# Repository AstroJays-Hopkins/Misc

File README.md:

# Misc

Small collection of utilities that don't have official repositories in the
Hopkins Rocketry Github org yet. These are experimental and may set your house on
fire, kill your pets, or do other horrible things. Consider yourself warned.

## DartPlot

(Avionics)

Visualize the runtime sensor logs (in our csv format).

## Schematics

(Avionics)

Temporary schematics until better quality ones can be drawn. Move these out as
they mature.

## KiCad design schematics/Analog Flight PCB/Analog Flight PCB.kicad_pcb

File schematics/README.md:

# Schematics

Temporary avionics schematics that haven't been reviewed yet, but need to be
saved for documentation purposes.

## Listing

- Ignition-System - Provisional ignition control box ("football") schematics.
  Inaccurate due to missing wires in football and broken conenctions.
- Prop-Avionics - Schematics for the propulsion avionics system and DAQ plane
- SolenoidRelay1 - Schematic for the solenoid control relay for connection to
  the raspberry pi.
- Transole - Prototype transistor based solenoid switching using GPIO level
  outputs and a heckin' large transistor (n-channel MOSFET). This is a *untested
  prototype* and should not be used in production until more research has been
  completed. Credit Sasha and Lin for research and design

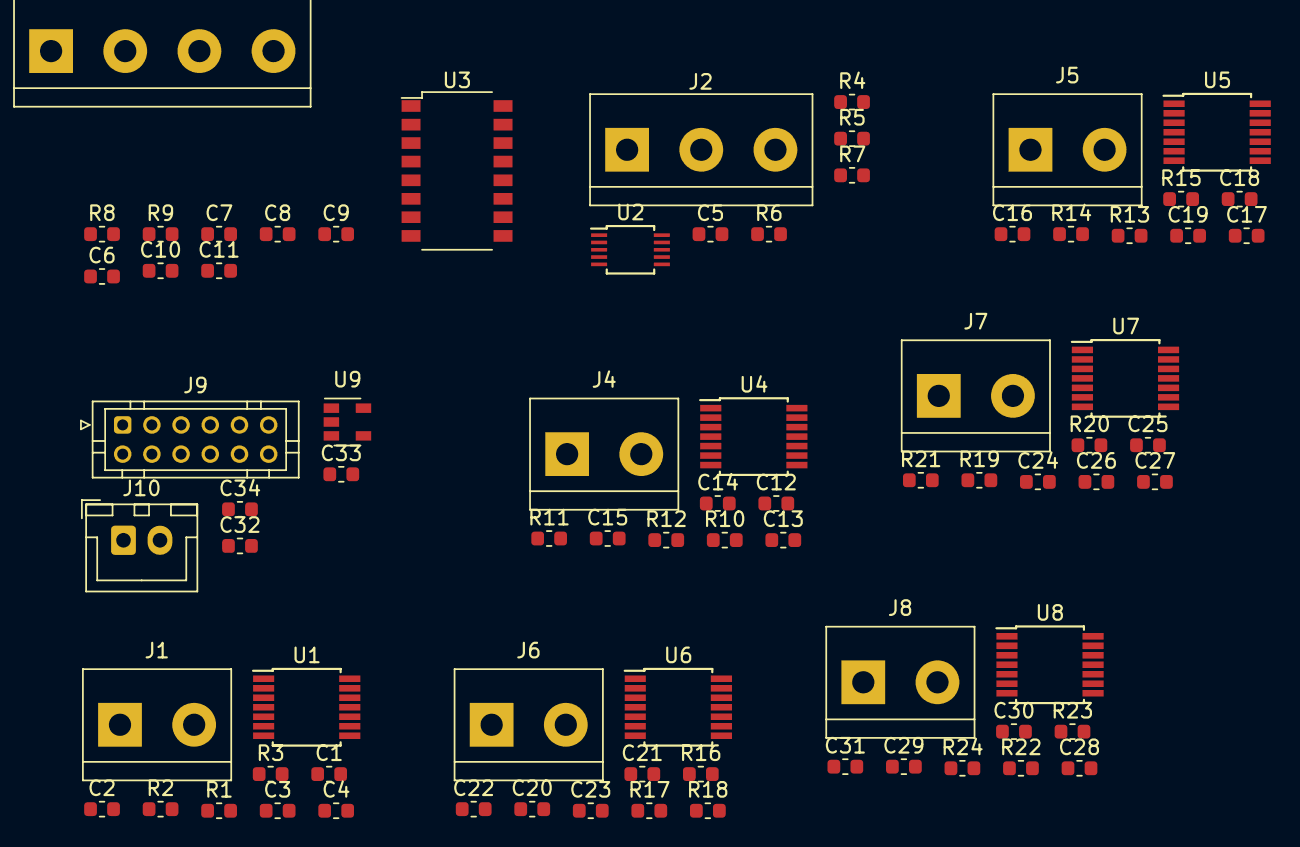
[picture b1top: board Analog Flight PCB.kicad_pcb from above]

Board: 2 copper layers, 77 parts (0 on the bottom side), 58 nets, no tracks yet.

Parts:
C1, C3, C12, C14, C16, C18, C20, C22, C24, C26, C28, C30, C34: 0.01u; C_0603_1608Metric
C2, C4, C6, C7, C10, C13, C15, C17, C19, C21, C23, C25, C27, C29, C31: 0.1u; C_0603_1608Metric
C5, C9, C11: 1u; C_0603_1608Metric
C8: 680p; C_0603_1608Metric
C32, C33: 2.2u; C_0603_1608Metric
J1, J4, J5, J6, J7, J8: Screw_Terminal_01x02; TerminalBlock_bornier-2_P5.08mm
J2: Screw_Terminal_01x03; TerminalBlock_bornier-3_P5.08mm
J3: Screw_Terminal_01x04; TerminalBlock_bornier-4_P5.08mm
J9: Conn_02x06_Top_Bottom; JST_PHD_B12B-PHDSS_2x06_P2.00mm_Vertical
J10: Conn_01x02_Male; JST_XH_B2B-XH-A_1x02_P2.50mm_Vertical
R1, R2, R3, R10, R11, R12, R13, R14, R15, R16, R17, R18, R19, R20, R21, R22, R23, R24: 2k; R_0603_1608Metric
R4, R5, R6, R7: 10k; R_0603_1608Metric
R8, R9: 47; R_0603_1608Metric
U1, U4, U5, U6, U7, U8: MAX31856; TSSOP-14_4.4x5mm_P0.65mm
U2: ADS1115IDGS; TSSOP-10_3x3mm_P0.5mm
U3: NAU7802SGI; SOP-16_4.4x10.4mm_P1.27mm
U9: LP2985-3.3; SOT-23-5

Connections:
+3V3: C4.1, C5.1, C15.1, C19.1, C23.1, C27.1, C31.1, C33.1, R4.1, R6.1, R7.1, U1.5, U1.8, U2.8, U4.5, U4.8, U5.5, U5.8, U6.5, U6.8, U7.5, U7.8, U8.5, U8.8, U9.5
+5V: C9.1, C32.1, J10.1, U3.15, U9.1, U9.3
/LC/SCL: J9.11, R6.2, U2.10, U3.13
/LC/SDA: J9.12, R7.2, U2.9, U3.14
/tc1/CS: J9.3, U1.9
/tc1/SCK: J9.1, U1.10, U4.10, U5.10, U6.10, U7.10, U8.10
/tc1/SDI: J9.2, U1.12, U4.12, U5.12, U6.12, U7.12, U8.12
/tc1/SDO: J9.7, U1.11, U4.11, U5.11, U6.11, U7.11, U8.11
/tc2/CS: J9.4, U4.9
/tc3/CS: J9.5, U5.9
/tc4/CS: J9.8, U6.9
/tc5/CS: J9.9, U7.9
/tc6/CS: J9.10, U8.9
GND: C1.1, C3.2, C4.2, C5.2, C7.2, C9.2, C10.2, C11.2, C12.1, C14.2, C15.2, C16.1, C18.2, C19.2, C20.1, C22.2, C23.2, C24.1, C26.2, C27.2, C28.1, C30.2, C31.2, C32.2, C33.2, C34.2, J3.4, J10.2, R5.1, U1.1, U1.14, U2.3, U3.7, U3.8, U3.9, U4.1, U4.14, U5.1, U5.14, U6.1, U6.14, U7.1, U7.14, U8.1, U8.14, U9.2
unnamed: C1.2, C2.1, R1.2, U1.4
unnamed: C2.2, C3.1, R2.1, U1.3
unnamed: C6.1, R8.1, U3.2
unnamed: C6.2, R9.1, U3.3
unnamed: C8.1, U3.4
unnamed: C8.2, U3.5
unnamed: C10.1, U3.6
unnamed: C7.1, C11.1, J3.1, U3.1, U3.16
unnamed: C12.2, C13.1, R10.2, U4.4
unnamed: C13.2, C14.1, R11.1, U4.3
unnamed: C16.2, C17.1, R13.2, U5.4
unnamed: C17.2, C18.1, R14.1, U5.3
unnamed: C20.2, C21.1, R16.2, U6.4
unnamed: C21.2, C22.1, R17.1, U6.3
unnamed: C24.2, C25.1, R19.2, U7.4
unnamed: C25.2, C26.1, R20.1, U7.3
unnamed: C28.2, C29.1, R22.2, U8.4
unnamed: C29.2, C30.1, R23.1, U8.3
unnamed: C34.1, U9.4
unnamed: J1.1, R1.1
unnamed: J1.2, R2.2, R3.2
unnamed: J2.1, U2.4
unnamed: J2.2, U2.5
unnamed: J2.3, U2.6
unnamed: J3.2, R8.2
unnamed: J3.3, R9.2
unnamed: J4.1, R10.1
unnamed: J4.2, R11.2, R12.2
unnamed: J5.1, R13.1
unnamed: J5.2, R14.2, R15.2
unnamed: J6.1, R16.1
unnamed: J6.2, R17.2, R18.2
unnamed: J7.1, R19.1
unnamed: J7.2, R20.2, R21.2
unnamed: J8.1, R22.1
unnamed: J8.2, R23.2, R24.2
unnamed: R3.1, U1.2
unnamed: R4.2, U2.2
unnamed: R5.2, U2.1
unnamed: R12.1, U4.2
unnamed: R15.1, U5.2
unnamed: R18.1, U6.2
unnamed: R21.1, U7.2
unnamed: R24.1, U8.2

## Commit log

2019-09-15 README.md: Initialize with descriptions
    A new future loooooms...
2019-09-15 .gitignore: Initialize with sane defaults
    Setup for python, Linux, Windows, and Mac
2019-09-15 Plotter: Add inital implementation
    Basic functionality has been achieved. More features will be added as
    necessary.
2019-09-15 Plotter: Update spec to 0.1.0
2019-09-24 Schamtics: Add initial thermocouple drawings
    Very WIP and footprints need cleaning.
2019-09-28 schemtics/thermocouples: Clean file structure
    Cleaned up backups and whatnot to make things nicer.
2019-09-28 Prop-Avionics: Modularize Schematic
    Break up components into sub schematics to make collaboration easier.
2019-09-28 Prop-Avionics: Add boilerplate
    Boilerplated solenoids and pressure transducers.
2019-09-29 .gitignore: Add KiCAD TEMPS
    Added *-cache.lib (library symbol caches) and *.sch-bak to the
    `.gitignore` file to prevent these from being included in commits. These
    are system specific caches that should not be shipped to the master
    repository.
2019-09-29 schematics: Add Prototype for Transistor Solenoid
    Added a schematic for the prototype transistor solenoid switching system
    to preserve documentation of work conducted today. This is an
    alternative to the (undocumented) relay switching system that was used
    previously.
2019-09-29 schematics/README.md: Update List
    Added Transole and Prop-Avionics To the listing of schematic projects
    contained within this repo.
2019-09-29 README: Correct typo(s)
2019-09-29 specs: Add README and Keywords
    This lays the framework for writing specifications in the future.
2019-09-29 specs: Add initial Propulsion Avionics Spec
2019-09-29 Schema: Add Solenoid Relay
    Both solenoids (normally open and normally closed) use this schematic.
    (Position of the pin changes for normally open/closed)
2019-09-29 Schema: added football
    Preliminary documentation of football ignition system,
    need fixes to panel wiring.
2019-09-29 Schema: added PT to PCB library
    Update to PCB library with new part used for PTs
2019-10-04 Flipped flyback diode.
2019-10-04 Modify symbol library table to remove system-specific library paths
2019-10-04 Schema: Flip flyback in relay
    Solenoidrelay schematic had backwards flyback diode.
2019-10-04 Schema: Update README
    Included `SolenoidRelay1` and `Ignition-System` in schematics listing.
2019-10-16 schema: Update Ignition-System
    Updated schematic to match current control surfaces and plans for
    extensions to the ground interface.
2019-10-19 specs: Add Meta-Guidelines
    Simple guidelines outlining what each specification must contain to be
    considered valid. Provisional document; to be updated as specifications
    standards on this team are refined.
2019-10-19 specs: Move DartPlot specs
    Moved DartPlot specs into the specifications folder and normalized
    heading to match the specs meta-spec.
2019-10-19 specs: Add Meta-Template
    Added template for specifications that also serve as an introduction to
    the amrkdown syntax.
2019-10-19 specs: Split out control plane
    Control Plane has been split into its own specification because it will
    probably grow.
2019-10-20 specs: Update Avionics C2 spec
    Updated to include new data about C2 plane packet format and
    awknowledgement and synchronization.
2019-10-20 specs: Update RF PRotocol
    Added details on packet types and how ack and sync packets should be
    processed. Also improved ACK packet description.
2019-10-20 specs: Update RF Valve command Codes
    Updated to makestandy state 0 so generic initializers can be used.
2019-10-24 specs: Update Valve Packet Format
    Updated with packet byte chart for clarification.
2019-10-24 Control Plane Spec: Update version number to 0.4.0
    Bump version due ot new changes.
2019-10-26 specs/Prop-Avionics: Update with I2C protocol defs
    Added basic I2c protocol specs to standardize implementation across all
    devices that will communicate on this bus. Design is still pending and
    may not work as speced.
2019-10-28 specs: Reorganize and add guides
    Moved all prop-avionics stuff into its own folder and added a new guide
    to bit manipulation.
2019-10-28 specs: Update I2C Spec
    Updated command spec to sepcify two bits for the vent states to allow
    the NOP state to be encoded in addition to the direction states.
2019-11-17 Create new schematics for Analog Flight PCBs.
    These schematics include the circuits for the thermocouples as well as the
    pressure transducers. Unlike previous iterations, they include resistors
    and capacitors necessary for the PCB.
2019-12-13 Updated schematics for Analog Flight PCB and drew preliminary schematics for Recovery PCB.
2019-12-21 Finish connecting analog flight PCB components and start PCB layout.
2019-12-21 Separated all components to make traces easier.
2019-12-22 Changed screw terminals to JST connectors and added two more connectors to the PTs.
2019-12-27 Finished layout for individual components and prepping for I2C and power connections.
2019-12-30 Preliminary PCB design for Analog Flight Board completed. Needs further review.
2019-12-31 Fixed loadcell connection and cleaned up references. Also replaced silk screen with edge cuts.
2020-01-17 Rerouted copper trace to intersect with other trace at via instead of three-point intersection; added datasheets for NAU7802SGI ADC chip and others.
2020-01-19 schema: Complete prelim. AFPCB design
    Preliminary PCB design for Analog Flight Board completed. Needs further
    review.
2020-01-19 ASPCB: Board cleanup
    Fixed loadcell connection and cleaned up references. Also replaced silk
    screen with edge cuts.
2020-01-19 ASPCB: Reroute and add datasheets
    Rerouted copper trace to intersect with other trace at via instead of
    three-point intersection; added datasheets for NAU7802SGI ADC chip and
    others.
2020-01-19 ASPCB: Move Loadcell.lib to Components.lib
    Moved loacell library to general components library and added fixed
    MAX31856 part with correct tristate SDO.
2020-01-19 schematics: Create Graphics lib
    Created new library for team-specific logos and graphics for PCBs.
2020-01-19 ASPCB: Revision 1.0c
    Changed all single row plug connectors to JST-PH instead of JST-XH to
    save space. All routes were optimized to place passives closer to ICs
    and contacts. Two additional LC reader assemblies were added for test
    config. Testpoints have been added on both 3v3 and 5v power supplies for
    testing. Power and ground have been moved into primary connector, with
    interleaving to preserve signal integrity. First attempt at a ground
2020-01-22 Added SAMD21G uC and crystal, RFM95 radio and supporting circuitry.
2020-01-26 .gitignore: Add more KiCAD Excludes
    Ignored more temporary, cahce, and system KiCAD files so they won't
    clutter the repo.
2020-01-26 ASPCB: Rev 1.0d
    Added three new TC ADCs per prop request. Loadcell interfaces had
    conflicting I2C addresses so a TI PCA9548 8ch I2C switch was added.
    PT supply voltage was changed from 3V3 to 5V. I2C level shifter using
    MOSFETs per Phillips AN97055 was added to ensure I2C bus reliability.
    Extra 5V power supply pin removed since one pin supplies up to 1A, far
    above the max current draw of this board. Traces have been rerouted for
2020-01-26 ASPCB: Rev 1.0e
    Optimized routing to prevent tombstoning. Analog trace lengths were
    further shortened, and extranious traces were removed. uCs have been
    renumbered to be fully consecutive.
2020-01-27 Added power uC RCL filter network and reset circuitry and preliminary circuitry for GPS module.
2020-02-12 Removed SD card level shifter, added pins and connections to GPS.
2020-02-12 schema: Restructure Lib
    Moved all footprints into new directory to prepare for new parts
2020-02-12 ASPCB: Rev 1.0g
    Final revision in the 1.0 series, adding power-on indicator and low pass
    filtering for ADC @ 1.59kHz to prevent aliasing. This revision is ready
    for fab and prototyping. Obsolete PCA9548A has been replaced by current
    part TCA9548A.
2020-02-12 ASPCB: Rev 1.0f
    Rerouted with DRDY select lines to I2C GPIO expander. This means that we
    can check all of the DRDY lines with one interrupt, so long as we poll
    the input expander after recieving each interrupt. This allows us to
    switch to interrupt driven programming, which should enhance the data
    collection speed while reducing CPU use. To accomodate the extra lines,
    we have switched to gridded ground style routing.
2020-02-12 schema/Lib: Add new parts
    Added 3d model for the JST connector and the new symbols and footprint
    for the ATSAMD21G
2020-02-12 Update actuator board schematic.
